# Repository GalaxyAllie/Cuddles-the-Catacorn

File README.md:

# Cuddles the Catacorn

Cuddles the Catacorn is the big sibling of 2020's [Candy the Catacorn](https://galaxyallie.space/Candy-the-Catacorn/).

- Mermaid tail PCB intended to be used with a hand-made mermaid body for customization.
- Raspberry Pi Pico used as a module to provide much functionality and enable easy assembly for beginners
- Intended completion April 2022
- Bright shiny things
- Gaming controls!
- [v1.69bis](https://hackaday.com/2019/03/20/introducing-the-shitty-add-on-v1-69bis-standard/) compliant-ish

## Bill of Materials

| Component                               | Manufacturer                 | Qty |
|-----------------------------------------|------------------------------|-----|
| This board                              | Whoever you choose           | 1   |
| Raspberry Pi Pico                       | Raspberry Pi                 | 1   |
| S2B-PH-SM4-TB(LF)(SN)                   | JST                          | 1   |
| 0.1uF 0805 Capacitor                    | Generic                      | 5   |
| WS2812b                                 | WorldSemi                    | 5   |
| LED 0805                                | Generic                      | 10  |
| DSS14UTR                                | SMC Diode Solutions          | 1   |
| 470 Ohm 0805 Resistor                   | Generic                      | 11  |
| TL3342 Switch (or equivalent)           | E-Switch (or generic)        | 6   |
| 2x3 2.54mm pin socket connector         | Generic                      | 1   |

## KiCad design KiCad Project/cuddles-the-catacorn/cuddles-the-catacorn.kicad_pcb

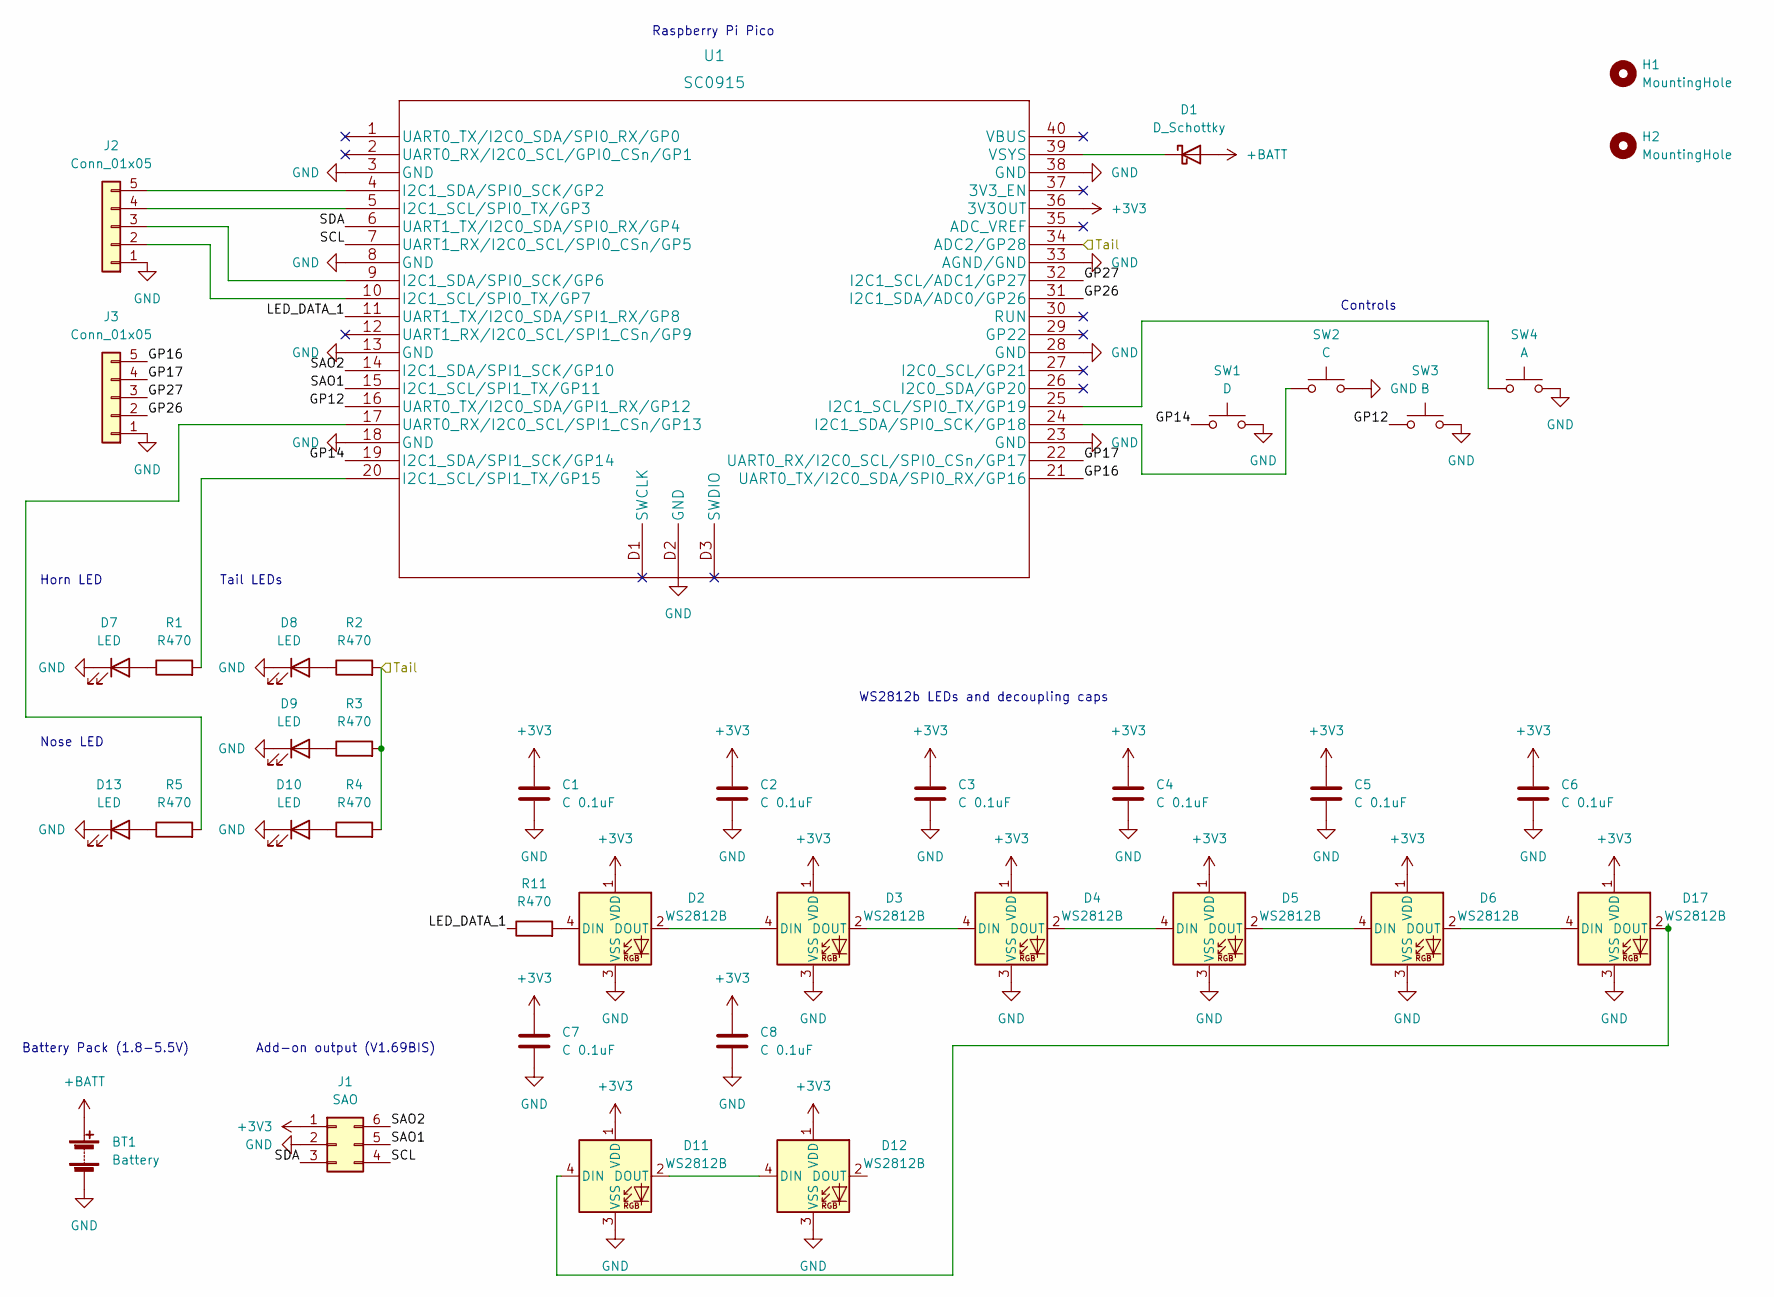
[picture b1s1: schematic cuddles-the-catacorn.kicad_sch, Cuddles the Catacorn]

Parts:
BT1: Battery; JST_PH_S2B-PH-SM4-TB_1x02-1MP_P2.00mm_Horizontal
C1, C2, C3, C4, C5, C6, C7, C8: C 0.1uF; C_0805_2012Metric_Pad1.18x1.45mm_HandSolder
D1: D_Schottky; D_SOD-123F
D2, D3, D4, D5, D6, D11, D12, D17: WS2812B; LED_WS2812B_PLCC4_5.0x5.0mm_P3.2mm
D7, D8, D9, D10, D13: LED; LED_0805_2012Metric_Pad1.15x1.40mm_HandSolder
H1, H2: MountingHole; MountingHole_2.2mm_M2_Pad
J1: SAO; PinSocket_2x03_P2.54mm_Vertical
J2, J3: Conn_01x05; PinHeader_1x05_P2.54mm_Vertical
R1, R2, R3, R4, R5, R11: R470; R_0805_2012Metric_Pad1.20x1.40mm_HandSolder
SW1: D; SW_SPST_TL3342
SW2: C; SW_SPST_TL3342
SW3: B; SW_SPST_TL3342
SW4: A; SW_SPST_TL3342
U1: SC0915; SC0915-No test pads

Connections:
+3V3: C1.1, C2.1, C3.1, C4.1, C5.1, C6.1, C7.1, C8.1, D2.1 (VDD), D3.1 (VDD), D4.1 (VDD), D5.1 (VDD), D6.1 (VDD), D11.1 (VDD), D12.1 (VDD), D17.1 (VDD), J1.1, U1.36 (3V3OUT)
+BATT: BT1.1 (+), D1.2 (A)
/GP12: SW3.1, U1.16 (UART0_TX/I2C0_SDA/GPI1_RX/GP12)
/GP14: SW1.1, U1.19 (I2C1_SDA/SPI1_SCK/GP14)
/GP16: J3.5, U1.21 (UART0_TX/I2C0_SDA/SPI0_RX/GP16)
/GP17: J3.4, U1.22 (UART0_RX/I2C0_SCL/SPI0_CSn/GP17)
/GP26: J3.2, U1.31 (I2C1_SDA/ADC0/GP26)
/GP27: J3.3, U1.32 (I2C1_SCL/ADC1/GP27)
/LED_DATA_1: R11.1, U1.11 (UART1_TX/I2C0_SDA/SPI1_RX/GP8)
/SAO1: J1.5, U1.15 (I2C1_SCL/SPI1_TX/GP11)
/SAO2: J1.6, U1.14 (I2C1_SDA/SPI1_SCK/GP10)
/SCL: J1.4, U1.7 (UART1_RX/I2C0_SCL/SPI0_CSn/GP5)
/SDA: J1.3, U1.6 (UART1_TX/I2C0_SDA/SPI0_RX/GP4)
/Tail: R2.2, R3.2, R4.2, U1.34 (ADC2/GP28)
GND: BT1.2 (-), C1.2, C2.2, C3.2, C4.2, C5.2, C6.2, C7.2, C8.2, D2.3 (VSS), D3.3 (VSS), D4.3 (VSS), D5.3 (VSS), D6.3 (VSS), D7.1 (K), D8.1 (K), D9.1 (K), D10.1 (K), D11.3 (VSS), D12.3 (VSS), D13.1 (K), D17.3 (VSS), J1.2, J2.1, J3.1, SW1.2, SW2.2, SW3.2, SW4.2, U1.3 (GND), U1.8 (GND), U1.13 (GND), U1.18 (GND), U1.23 (GND), U1.28 (GND), U1.33 (AGND/GND), U1.38 (GND), U1.D2 (GND)
unnamed: D1.1 (K), U1.39 (VSYS)
unnamed: D2.2 (DOUT), D3.4 (DIN)
unnamed: D2.4 (DIN), R11.2
unnamed: D3.2 (DOUT), D4.4 (DIN)
unnamed: D4.2 (DOUT), D5.4 (DIN)
unnamed: D5.2 (DOUT), D6.4 (DIN)
unnamed: D6.2 (DOUT), D17.4 (DIN)
unnamed: D7.2 (A), R1.1
unnamed: D8.2 (A), R2.1
unnamed: D9.2 (A), R3.1
unnamed: D10.2 (A), R4.1
unnamed: D11.2 (DOUT), D12.4 (DIN)
unnamed: D13.2 (A), R5.1
unnamed: D11.4 (DIN), D17.2 (DOUT)
unnamed: R1.2, U1.20 (I2C1_SCL/SPI1_TX/GP15)
unnamed: SW2.1, U1.24 (I2C1_SDA/SPI0_SCK/GP18)
unnamed: SW4.1, U1.25 (I2C1_SCL/SPI0_TX/GP19)
unnamed: J2.5, U1.4 (I2C1_SDA/SPI0_SCK/GP2)
unnamed: J2.4, U1.5 (I2C1_SCL/SPI0_TX/GP3)
unnamed: J2.3, U1.9 (I2C1_SDA/SPI0_SCK/GP6)
unnamed: J2.2, U1.10 (I2C1_SCL/SPI0_TX/GP7)
unnamed: R5.2, U1.17 (UART0_RX/I2C0_SCL/SPI1_CSn/GP13)

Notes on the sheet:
Add-on output (V1.69BIS)
Nose LED
Controls
Battery Pack (1.8-5.5V)
Raspberry Pi Pico
WS2812b LEDs and decoupling caps
Horn LED
Tail LEDs

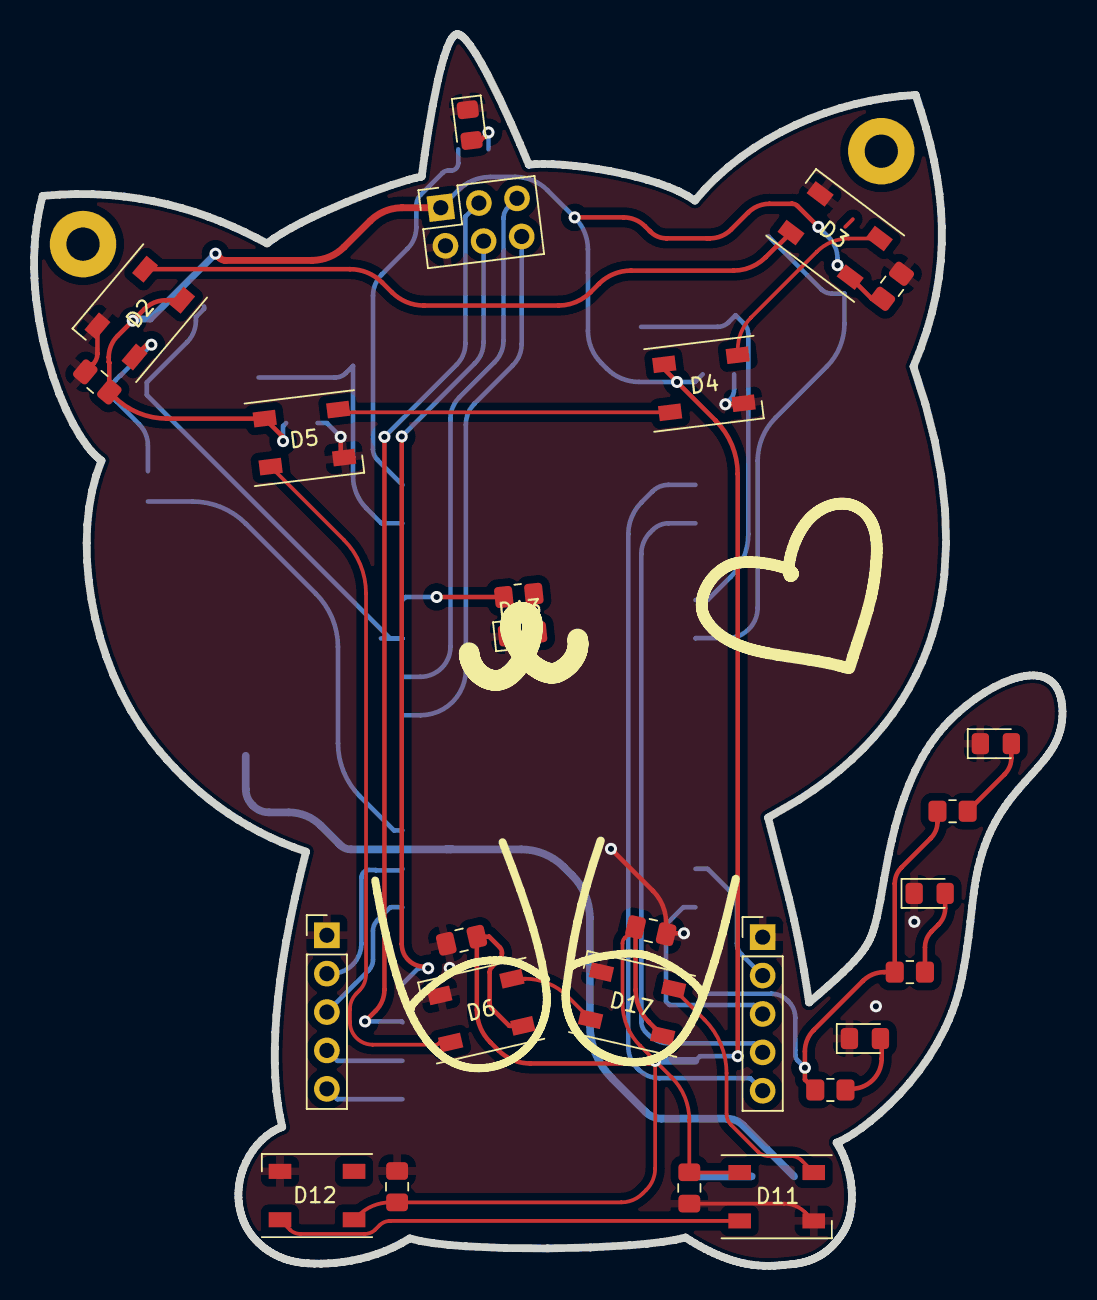
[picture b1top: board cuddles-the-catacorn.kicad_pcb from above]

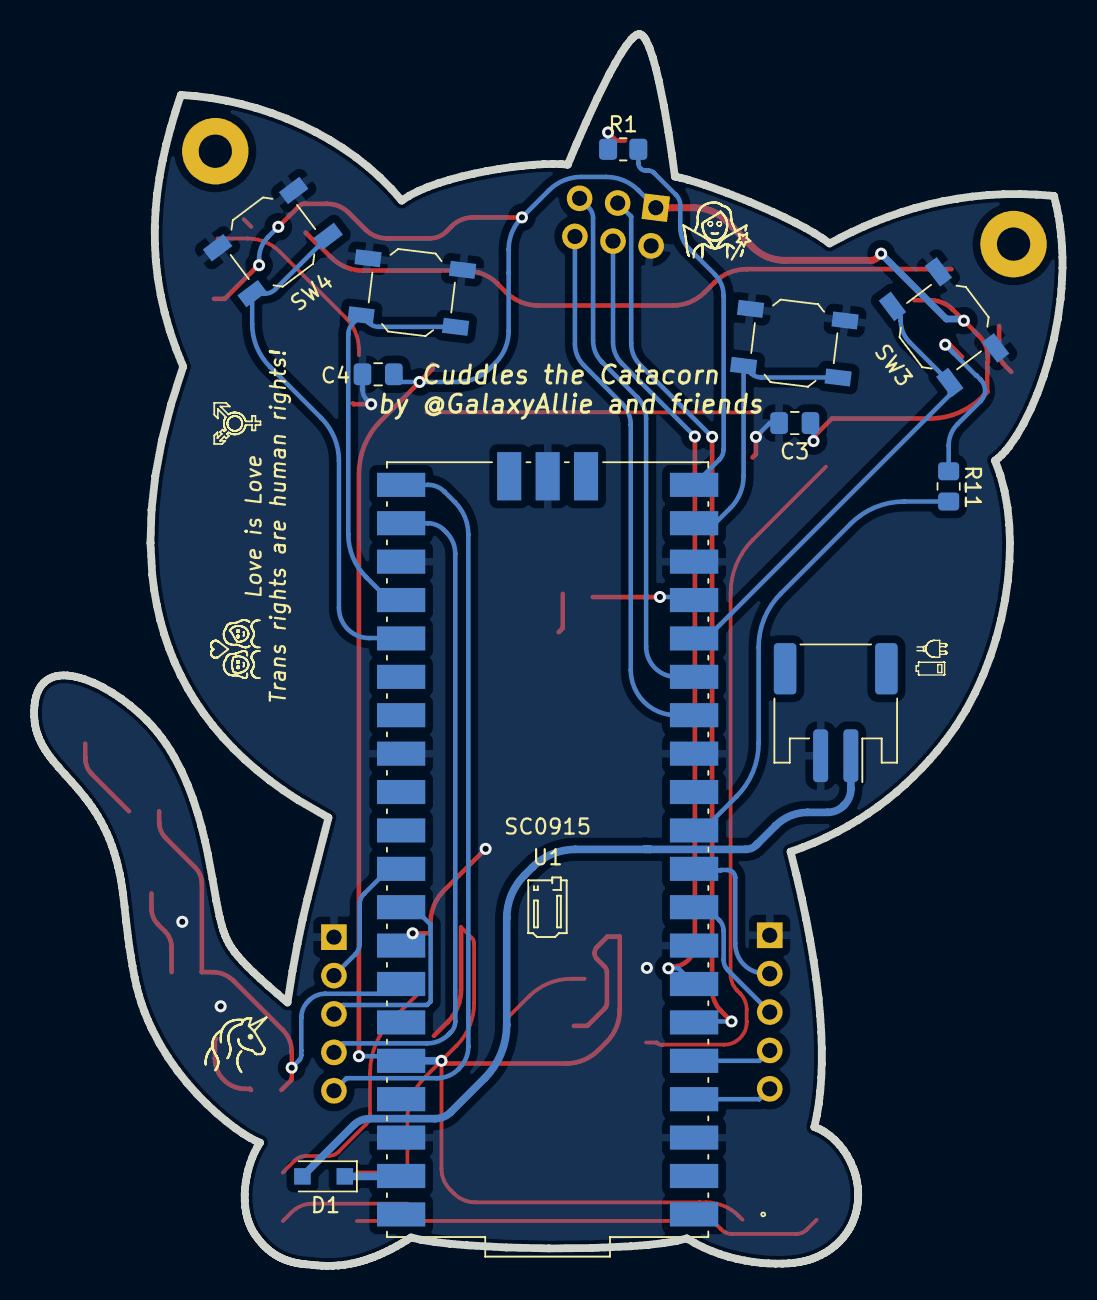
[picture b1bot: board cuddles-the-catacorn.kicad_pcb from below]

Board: 2 copper layers, 68.0 x 81.5 mm, 39 parts (11 on the bottom side), 37 nets.

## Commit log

2022-01-25 Added Candy artwork
2022-01-25 First draft
2022-01-25 Schematic changes to simplify routing
2022-01-25 DRC errors cleared

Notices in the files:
parts and their libraries:
Copyright 2021 Accelerated Designs. All rights reserved.
